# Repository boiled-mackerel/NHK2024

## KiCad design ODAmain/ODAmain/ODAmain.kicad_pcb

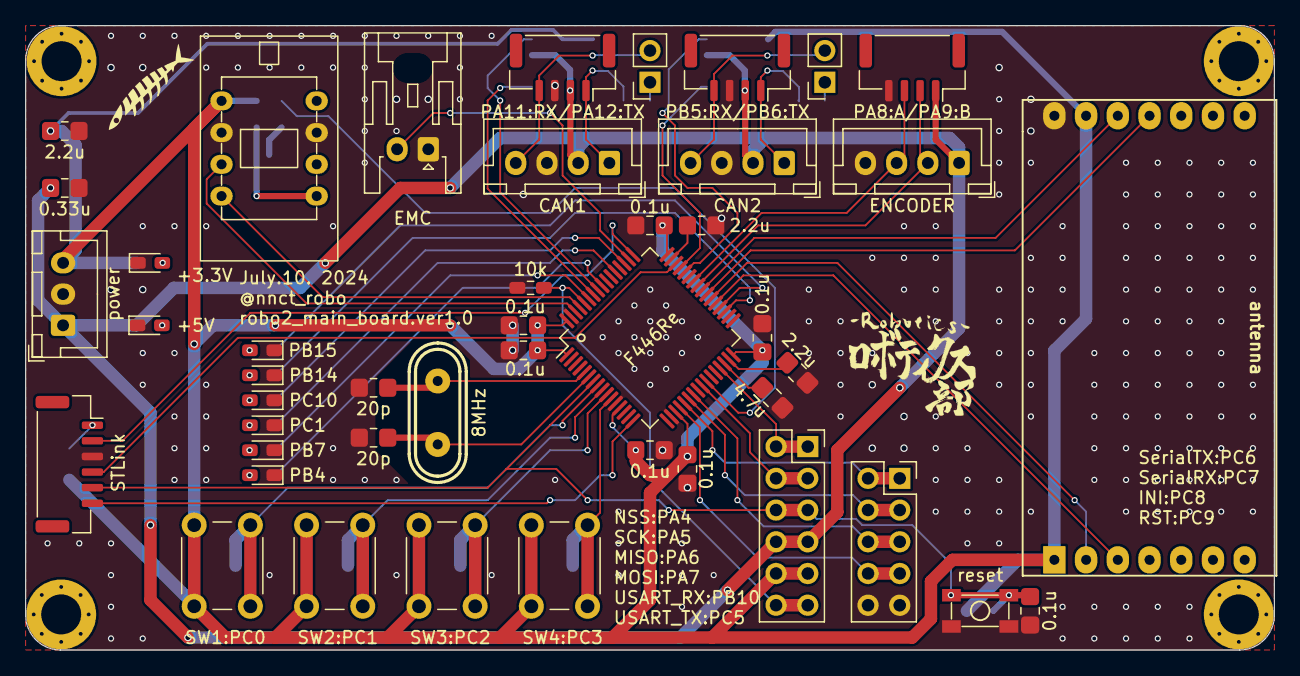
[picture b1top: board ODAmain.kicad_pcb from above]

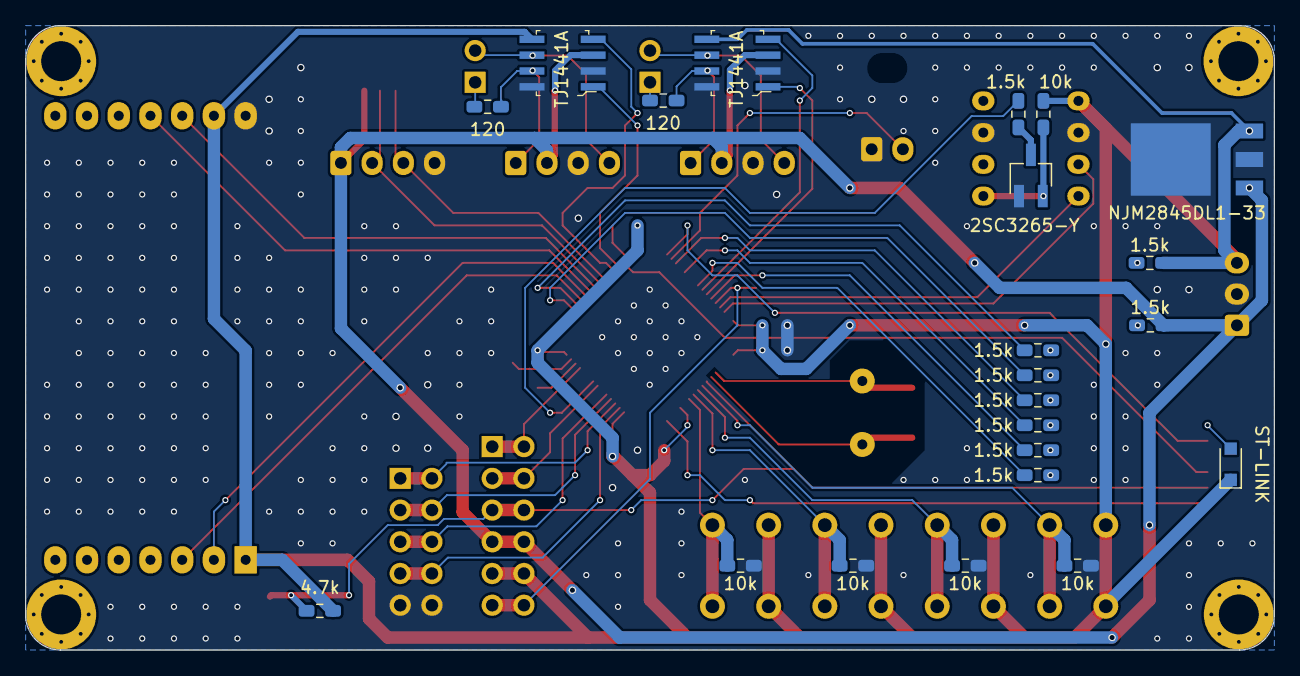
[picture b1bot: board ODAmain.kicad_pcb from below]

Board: 2 copper layers, 100.0 x 50.0 mm, 67 parts (22 on the bottom side), 60 nets.

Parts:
C1: 0.33u; C_0805_2012
C2, C14, C15: 2.2u; C_0805_2012
C3, C6, C8, C9, C10, C11, C12: 0.1u; C_0805_2012
C4, C5: 20p; C_0805_2012
C7: 4.7u; C_0805_2012
D1: PB4; LED_0603_1608
D2: PB7; LED_0603_1608
D3: PC1; LED_0603_1608
D4: PC10; LED_0603_1608
D5: PB14; LED_0603_1608
D6: PB15; LED_0603_1608
D7: +5V; LED_0603_1608
D8: +3.3V; LED_0603_1608
J1: Conn_02x06_Counter_Clockwise; PinSocket_2x06_P2.54mm_Vertical
J2: Conn_02x05_Counter_Clockwise; PinSocket_2x05_P2.54mm_Vertical
J3: Terminate_CAN1; PinSocket_1x02_P2.54mm_Vertical
J4: Terminate_CAN2; PinSocket_1x02_P2.54mm_Vertical
J5: EMC; JST_XA_S02B-XASK-1_1x02_P2.50mm_Horizontal
J6: CAN_1; JST_XH_B4B-XH-A_1x04_P2.50mm_Vertical
J7: CAN_2; JST_XH_B4B-XH-A_1x04_P2.50mm_Vertical
J8: ENCODER1; JST_XH_B4B-XH-A_1x04_P2.50mm_Vertical
J9: gh:CAN_1; JST_GH_SM04B-GHS-TB_1x04-1MP_P1.25mm_Horizontal
J10: gh:CAN_2; JST_GH_SM04B-GHS-TB_1x04-1MP_P1.25mm_Horizontal
J11: gh:ENCODER1; JST_GH_SM04B-GHS-TB_1x04-1MP_P1.25mm_Horizontal
Q1: 2SC3265-Y; 2sc3265_SC-59_Handsoldering
R1, R2: 120; R_0603_1608
R3, R4, R5, R6, R7, R8, R9, R10, R11: 1.5k; R_0603_1608
R12: 4.7k; R_0603_1608
R13, R14, R15, R16, R17, R18: 10k; R_0603_1608
SW1:PC0, SW2:PC1, SW3:PC2, SW4:PC3: SW_Push; SW_PUSH_6mm
U1, U2: TJA1441AT; SOIC-8_IR2302_TJA1441AT
U3: D_Schottky; smd_diode_SOD-323_HandSoldering_cus10f30
U4: power; JST_XH_B3B-XH-A_1x03_P2.50mm_Vertical
U5: ST-LINK; JST_GH_SM06B-GHS-TB_1x06-1MP_P1.25mm_Horizontal
U6: NJM2845DL1-33
U7: BNO055
U8: reset; tact_sw_smd_skrpabe10
U9: FEP-02; FEP-02_PIN_SOCKET
U11: STM32F446RETx-stm32; LQFP-64_10x10mm_P0.5mm
Y1: 8MHz; crystal_hc-49u

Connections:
+3.3V: C2.1, C6.1, C8.1, C9.1, C10.1, C11.1, C12.1, J1.9, J1.10, R10.1, R12.1, R13.2, SW1:PC0.1, SW2:PC1.1, SW3:PC2.1, SW4:PC3.1, U1.5 (VIO), U2.5 (VIO), U3.1 (K), U4.3, U6.3 (Vout), U7.1 (VIN), U9.1 (VCC(2.5v-5.5v)), U9.13 (PowerOn), U11.1 (VBAT), U11.13 (VDDA), U11.19 (VDD), U11.32 (VDD), U11.48 (VDD), U11.64 (VDD)
+5V: C1.1, J1.7, J1.8, J6.2, J7.2, J8.1, J9.2, J10.2, J11.1, R9.1, U1.3 (VDD), U2.3 (VDD), U4.1, U6.1 (Vin)
BNO_RESET: R11.1, U11.26 (ADC1_IN8/ADC2_IN8/I2S3_SD/SDIO_D1/SPI3_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)
BNO_SCL: U7.4 (SCL), U11.61 (CAN1_RX/DCMI_D6/I2C1_SCL/SDIO_D4/TIM10_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)
BNO_SDA: U7.3 (SDA), U11.62 (CAN1_TX/DAC_EXTI9/DCMI_D7/I2C1_SDA/I2S2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)
BOOT0: J1.11, J1.12, R18.2, U11.60 (BOOT0)
CAN1H: J6.1, J9.1, R1.1, U1.7 (CANH)
CAN1L: J3.2, J6.4, J9.4, U1.6 (CANL)
CAN2H: J7.1, J10.1, R2.1, U2.7 (CANH)
CAN2L: J4.2, J7.4, J10.4, U2.6 (CANL)
D4_CAN2RX: U2.4 (RXD), U11.57 (CAN2_RX/DCMI_D10/I2C1_SMBA/I2S1_SD/I2S3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)
D10_CAN2TX: U2.1 (TXD), U11.58 (CAN2_TX/CEC/DCMI_D5/I2C1_SCL/QUADSPI_BK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)
D14_CAN1TX: U1.1 (TXD), U11.45 (CAN1_TX/TIM1_ETR/USART1_RTS/USB_OTG_FS_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)
D15_CAN1RX: U1.4 (RXD), U11.44 (ADC1_EXTI11/ADC2_EXTI11/ADC3_EXTI11/CAN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)
EMC: J5.2, U11.50 (ADC1_EXTI15/ADC2_EXTI15/ADC3_EXTI15/CEC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)
FEP_INI: U9.11 (/INI), U11.39 (PC8/DCMI_D2/SDIO_D0/SYS_TRACED0/TIM3_CH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)
FEP_RST: U9.12 (/RST), U11.40 (PC9/DAC_EXTI9/DCMI_D3/I2C3_SDA/I2S_CKIN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)
GND: C1.2, C2.2, C3.2, C4.1, C5.1, C6.2, C7.2, C8.2, C9.2, C10.2, C11.2, C12.2, C14.2, C15.2, D1.1 (K), D2.1 (K), D3.1 (K), D4.1 (K), D5.1 (K), D6.1 (K), D7.1 (K), D8.1 (K), J2.9, J2.10, J5.1, J6.3, J7.3, J8.4, J9.3, J10.3, J11.4, Q1.1 (E), R14.2, R15.2, R16.2, R17.2, R18.1, U1.2 (GND), U1.8 (S), U2.2 (GND), U2.8 (S), U4.2, U5.3, U6.2 (GND), U7.2 (GND), U7.7 (GND), U8.2, U8.4, U9.14 (GND), U11.12 (VSSA), U11.18 (VSS), U11.63 (VSS)
LED1: R8.1, U11.36 (ADC1_EXTI15/ADC2_EXTI15/ADC3_EXTI15/I2S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)
LED2: R7.1, U11.35 (SPI2_MISO/TIM12_CH1/TIM1_CH2N/TIM8_CH2N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)
LED3: R6.1, U11.51 (PC10/DCMI_D8/I2S3_CK/QUADSPI_BK1_IO1/SD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)
LED4: R5.1, U11.53 (PC12/DCMI_D9/I2C2_SDA/I2S3_SD/SDIO_CK/S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)
LED5: R4.1, U11.59 (DCMI_VSYNC/I2C1_SDA/SPDIFRX_IN0/TIM4_CH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)
LED6: R3.1, U11.56 (I2C3_SDA/I2S2_WS/SPI1_MISO/SPI2_NSS/SPI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)
MISO: J2.3, J2.4, U11.22 (ADC1_IN6/ADC2_IN6/DCMI_PIXCLK/I2S2_MCK/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)
MOSI: J2.5, J2.6, U11.23 (ADC1_IN7/ADC2_IN7/I2S1_SD/SPI1_MOSI/TIM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)
NSS: J2.7, J2.8, U11.20 (ADC1_IN4/ADC2_IN4/DAC_OUT1/DCMI_HSYNC/I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)
unnamed: C14.1, U11.47 (VSS)
unnamed: C15.1, U11.31 (VSS)
unnamed: D1.2 (A), R3.2
unnamed: D2.2 (A), R4.2
unnamed: D3.2 (A), R5.2
unnamed: D4.2 (A), R6.2
unnamed: D5.2 (A), R7.2
unnamed: D6.2 (A), R8.2
unnamed: D7.2 (A), R9.2
unnamed: D8.2 (A), R10.2
unnamed: J3.1, R1.2
unnamed: J4.1, R2.2
unnamed: Q1.3 (B), R11.2
unnamed: Q1.2 (C), R13.1, U7.5 (RESET)
unnamed: U3.2 (A), U5.1
unnamed: C4.2, U11.5 (PH0/RCC_OSC_IN), Y1.2
unnamed: C5.2, U11.6 (PH1/RCC_OSC_OUT), Y1.1
unnamed: C7.1, U11.30 (VCAP_1)
PC_6_Serial6TX: U9.3 (TXD(DataIn)), U11.37 (PC6/DCMI_D0/FMPI2C1_SCL/I2S2_MCK/SDIO_D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)
PC_7_Serial6RX: U9.2 (RXD(DateOut)), U11.38 (PC7/DCMI_D1/FMPI2C1_SDA/I2S2_CK/I2S3_MC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)
RESET: C3.1, J1.5, J1.6, R12.2, U5.5, U8.1, U8.3, U11.7 (NRST)
SCK: J2.1, J2.2, U11.21 (ADC1_IN5/ADC2_IN5/DAC_OUT2/I2S1_CK/SPI1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)
ST-LINK(TX): U5.6, U11.16 (ADC1_IN2/ADC2_IN2/ADC3_IN2/TIM2_CH3/TIM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)
SW1: R14.1, SW1:PC0.2, U11.8 (PC0/ADC1_IN10/ADC2_IN10/ADC3_IN10/SAI1_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)
SW2: R15.1, SW2:PC1.2, U11.9 (PC1/ADC1_IN11/ADC2_IN11/ADC3_IN11/I2S2_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)
SW3: R16.1, SW3:PC2.2, U11.10 (PC2/ADC1_IN12/ADC2_IN12/ADC3_IN12/SPI2_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)
SW4: R17.1, SW4:PC3.2, U11.11 (PC3/ADC1_IN13/ADC2_IN13/ADC3_IN13/I2S2_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)
SWCLK: U5.2, U11.49 (SYS_JTCK-SWCLK/PA14)
SWDIO: U5.4, U11.46 (SYS_JTMS-SWDIO/PA13)
TIM1_1: J8.2, J11.2, U11.41 (I2C3_SCL/RCC_MCO_1/TIM1_CH1/USART1_CK/U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)
TIM1_2: J8.3, J11.3, U11.42 (DAC_EXTI9/DCMI_D0/I2C3_SMBA/I2S2_CK/SAI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)
U0RXD: J1.1, J1.2, U11.29 (I2C2_SCL/I2S2_CK/SAI1_SCK_A/SPI2_SCK/TI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)
U0TXD: J1.3, J1.4, U11.25 (PC5/ADC1_IN15/ADC2_IN15/SPDIFRX_IN3/USA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)

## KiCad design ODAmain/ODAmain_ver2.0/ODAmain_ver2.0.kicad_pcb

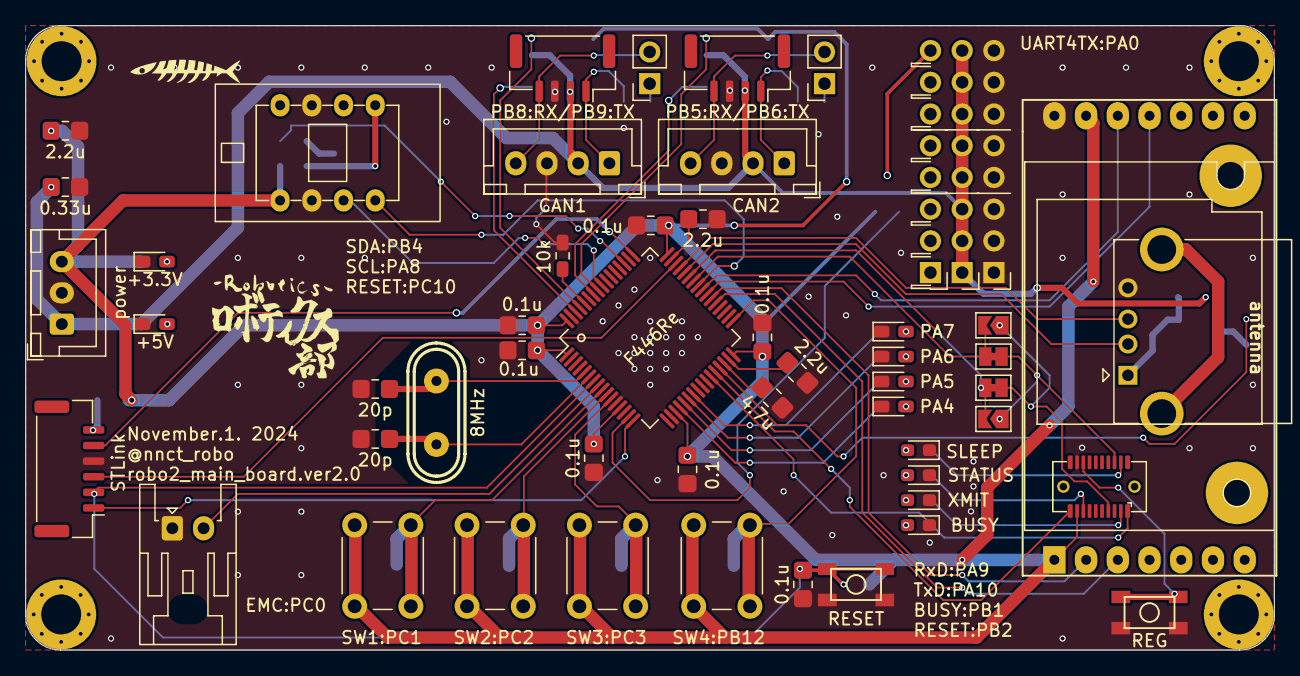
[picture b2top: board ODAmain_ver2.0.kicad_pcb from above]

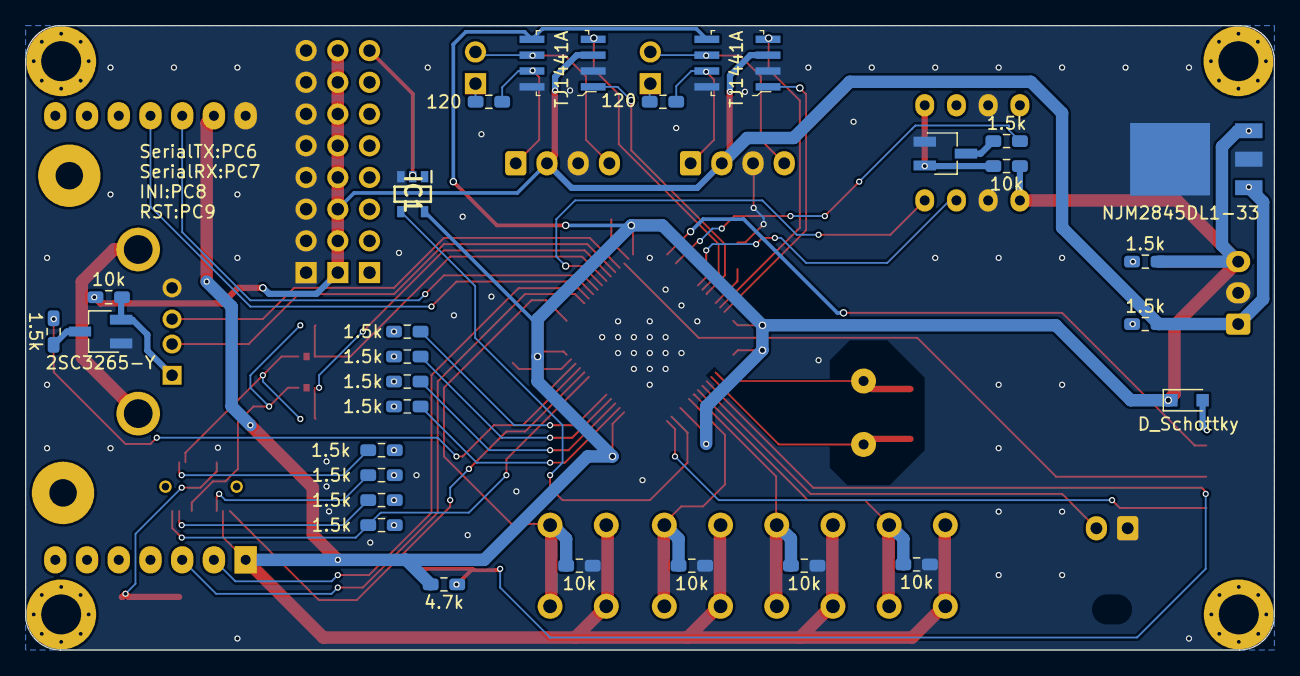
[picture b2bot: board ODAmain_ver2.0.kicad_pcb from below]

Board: 2 copper layers, 100.0 x 50.0 mm, 79 parts (28 on the bottom side), 69 nets.

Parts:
C1: 0.33u; C_0805_2012
C2, C8, C9: 2.2u; C_0805_2012
C3, C6, C10, C11, C12, C13, C14: 0.1u; C_0805_2012
C4, C5: 20p; C_0805_2012
C7: 4.7u; C_0805_2012
D3: PA7; LED_0603_1608
D4: PA6; LED_0603_1608
D5: PA5; LED_0603_1608
D6: PA4; LED_0603_1608
D7: +5V; LED_0603_1608
D8: +3.3V; LED_0603_1608
D9: BUSY; LED_0603_1608Metric_Pad1.05x0.95mm_HandSolder
D10: XMIT; LED_0603_1608Metric_Pad1.05x0.95mm_HandSolder
D11: SLEEP; LED_0603_1608Metric_Pad1.05x0.95mm_HandSolder
D12: STATUS; LED_0603_1608Metric_Pad1.05x0.95mm_HandSolder
IC1: BD7LS04G-CTL; SOT95P280X125-5N
J1: EMC; JST_XA_S02B-XASK-1_1x02_P2.50mm_Horizontal
J2: Terminate_CAN1; PinSocket_1x02_P2.54mm_Vertical
J3: Terminate_CAN2; PinSocket_1x02_P2.54mm_Vertical
J4: CAN_1; JST_XH_B4B-XH-A_1x04_P2.50mm_Vertical
J5: CAN_2; JST_XH_B4B-XH-A_1x04_P2.50mm_Vertical
J6: gh:CAN_1; JST_GH_SM04B-GHS-TB_1x04-1MP_P1.25mm_Horizontal
J7: gh:CAN_2; JST_GH_SM04B-GHS-TB_1x04-1MP_P1.25mm_Horizontal
J8: im920sl_USB; USB_A_CONNFLY_DS1095-WNR0
J9: RX==TX; SolderJumper-2_P1.3mm_Bridged_Pad1.0x1.5mm
J10: TX==RX; SolderJumper-2_P1.3mm_Bridged_Pad1.0x1.5mm
J11: RX==RX; SolderJumper-2_P1.3mm_Open_TrianglePad1.0x1.5mm
J12: TX==TX; SolderJumper-2_P1.3mm_Open_TrianglePad1.0x1.5mm
Q1, Q2: 2SC3265-Y; 2sc3265_SC-59_Handsoldering
R2, R3: 120; R_0603_1608
R5, R6, R7, R8, R9, R10, R11, R13, R16, R17, R18, R19: 1.5k; R_0603_1608
R12, R14, R20, R21, R22, R23, R24: 10k; R_0603_1608
R15: 4.7k; R_0603_1608
SW1: SW1:PC1; SW_PUSH_6mm
SW2: SW2:PC2; SW_PUSH_6mm
SW3: SW3:PC3; SW_PUSH_6mm
SW4: SW4:PB12; SW_PUSH_6mm
U1: D_Schottky; smd_diode_SOD-323_HandSoldering_cus10f30
U2, U3: TJA1441AT; SOIC-8_IR2302_TJA1441AT
U4: power; JST_XH_B3B-XH-A_1x03_P2.50mm_Vertical
U5: ST-LINK; JST_GH_BM06B-GHS-TBT_1x06-1MP_P1.25mm_Vertical
U6: NJM2845DL1-33
U7: BNO055
U8: FEP-02; FEP-02_PIN_SOCKET
U9: IM920sL
U10: RESET; tact_sw_smd_skrpabe10
U11: REG; tact_sw_smd_skrpabe10
U12: R3006SB
U13: stm32_f446re; LQFP-64_10x10mm_P0.5mm
Y1: 8MHz; crystal_hc-49u

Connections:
+3.3V: C2.1, C6.1, C10.1, C11.1, C12.1, C13.1, C14.1, IC1.5 (VCC), R13.1, R14.2, R15.1, SW1.1, SW2.1, SW3.1, SW4.1, U1.1 (K), U2.5 (VIO), U3.5 (VIO), U4.3, U6.3 (Vout), U7.1 (VIN), U8.1 (VCC(2.5v-5.5v)), U8.13 (PowerOn), U9.17 (VCC), U13.1 (VBAT), U13.13 (VDDA), U13.19 (VDD), U13.32 (VDD), U13.48 (VDD), U13.64 (VDD)
+5V: C1.1, J4.2, J5.2, J6.2, J7.2, R10.1, R12.2, U2.3 (VDD), U3.3 (VDD), U4.1, U6.1 (Vin), U12.2 (5V)
BNO_RESET: R11.1, U13.51 (PC10)
BNO_SCL: U7.4 (SCL), U13.41 (PA8)
BNO_SDA: U7.3 (SDA), U13.56 (PB4)
BOOT0: R24.2, U13.60 (BOOT0)
CAN1H: J4.1, J6.1, R2.1, U2.7 (CANH)
CAN1L: J2.2, J4.4, J6.4, U2.6 (CANL)
CAN1_RX: U2.4 (RXD), U13.61 (PB8)
CAN1_TX: U2.1 (TXD), U13.62 (PB9)
CAN2H: J5.1, J7.1, R3.1, U3.7 (CANH)
CAN2L: J3.2, J5.4, J7.4, U3.6 (CANL)
CAN2_RX: U3.4 (RXD), U13.57 (PB5)
CAN2_TX: U3.1 (TXD), U13.58 (PB6)
EMC: J1.2, U13.8 (PC0)
FEP_INI: U8.11 (/INI), U13.39 (PC8)
FEP_RST: U8.12 (/RST), U13.40 (PC9)
GND: C1.2, C2.2, C3.2, C4.1, C5.1, C6.2, C7.2, C8.2, C9.2, C10.2, C11.2, C12.2, C13.2, C14.2, D3.1 (K), D4.1 (K), D5.1 (K), D6.1 (K), D7.1 (K), D8.1 (K), D9.1 (K), D10.1 (K), D11.1 (K), D12.1 (K), IC1.3 (GND), J1.1, J4.3, J5.3, J6.3, J7.3, J8.4 (GND), Q1.1 (E), Q2.1 (E), R20.2, R21.2, R22.2, R23.2, R24.1, U2.2 (GND), U2.8 (S), U3.2 (GND), U3.8 (S), U4.2, U5.4, U6.2 (GND), U7.2 (GND), U7.7 (GND), U8.14 (GND), U9.18 (GND), U10.2, U10.4, U11.2, U11.4, U12.1 (GND), U13.12 (VSSA), U13.18 (VSS), U13.63 (VSS)
LED1: R8.1, U13.20 (PA4)
LED2: R7.1, U13.21 (PA5)
LED3: R6.1, U13.22 (PA6)
LED4: R5.1, U13.23 (PA7)
unnamed: C8.1, U13.31 (VSS)
unnamed: C9.1, U13.47 (VSS)
unnamed: D3.2 (A), R5.2
unnamed: D4.2 (A), R6.2
unnamed: D5.2 (A), R7.2
unnamed: D6.2 (A), R8.2
unnamed: D7.2 (A), R10.2
unnamed: D8.2 (A), R13.2
unnamed: D9.2 (A), R16.2
unnamed: D10.2 (A), R17.2
unnamed: D11.2 (A), R18.2
unnamed: D12.2 (A), R19.2
unnamed: J2.1, R2.2
unnamed: J3.1, R3.2
unnamed: J8.1 (VBUS), Q1.2 (C), R12.1
unnamed: J10.2, J11.2, U13.43 (PA10)
unnamed: J9.2, J12.2, U13.42 (PA9)
unnamed: Q1.3 (B), R9.2
unnamed: Q2.3 (B), R11.2
unnamed: Q2.2 (C), R14.1, U7.5 (RESET)
unnamed: U1.2 (A), U5.6
unnamed: R17.1, U9.3 (IO3/XMIT)
unnamed: R18.1, U9.4 (IO4/SLEEP)
unnamed: U9.16 (REG), U11.1, U11.3
unnamed: R19.1, U9.15 (SATUS)
unnamed: C4.2, U13.5 (PH0), Y1.2
unnamed: C5.2, U13.6 (PH1), Y1.1
unnamed: C7.1, U13.30 (VCAP_1)
PC_6_Serial6TX: U8.3 (TXD(DataIn)), U13.37 (PC6)
PC_7_Serial6RX: U8.2 (RXD(DateOut)), U13.38 (PC7)
RST: C3.1, R15.2, U5.2, U10.1, U10.3, U13.7 (NRST)
SBUS: IC1.2 (A), U12.10 (S.BUS)
SW1: R20.1, SW1.2, U13.9 (PC1)
SW2: R21.1, SW2.2, U13.10 (PC2)
SW3: R22.1, SW3.2, U13.11 (PC3)
SW4: R23.1, SW4.2, U13.33 (PB12)
SWCLK: U5.5, U13.49 (PA14)
SWDIO: U5.3, U13.46 (PA13)
UART2_TX(STLINK): U5.1, U13.16 (PA2)
UART4_RX: IC1.4 (Y), U13.15 (PA1)
im920sl_BUSY: R16.1, U9.1 (BUSY), U13.27 (PB1)
im920sl_D+: J8.3 (D+), U13.45 (PA12)
im920sl_D-: J8.2 (D-), U13.44 (PA11)
im920sl_RESET: U9.19 (RESET), U13.28 (PB2)
im920sl_RxD: J9.1, J11.1, U9.6 (RxD)
im920sl_TxD: J10.1, J12.1, U9.7 (TxD)
im920sl_zettairesetsaseruMAN: R9.1, U13.29 (PB10)

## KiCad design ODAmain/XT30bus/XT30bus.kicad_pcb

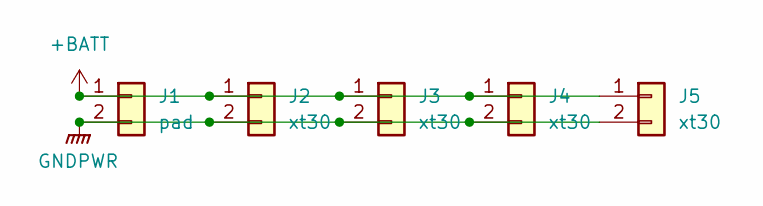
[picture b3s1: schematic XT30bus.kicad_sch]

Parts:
J1: pad; POWER_PAD_normal
J2, J3, J4, J5: xt30; AMASS_XT30U-F_1x02_P5.0mm_Vertical

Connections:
+BATT: J1.1, J2.1, J3.1, J4.1, J5.1
GNDPWR: J1.2, J2.2, J3.2, J4.2, J5.2

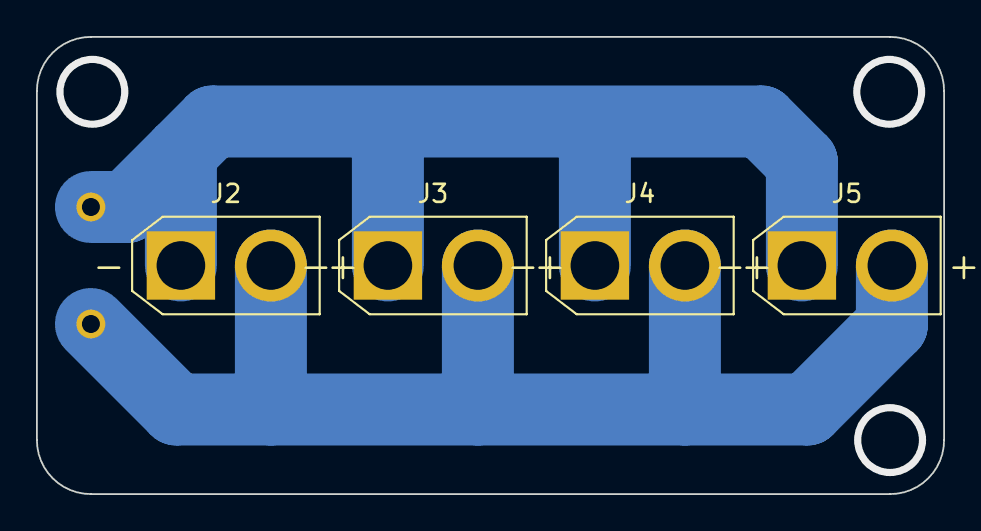
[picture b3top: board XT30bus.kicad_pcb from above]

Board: 2 copper layers, 50.4 x 25.4 mm, 5 parts (1 on the bottom side), 2 nets.

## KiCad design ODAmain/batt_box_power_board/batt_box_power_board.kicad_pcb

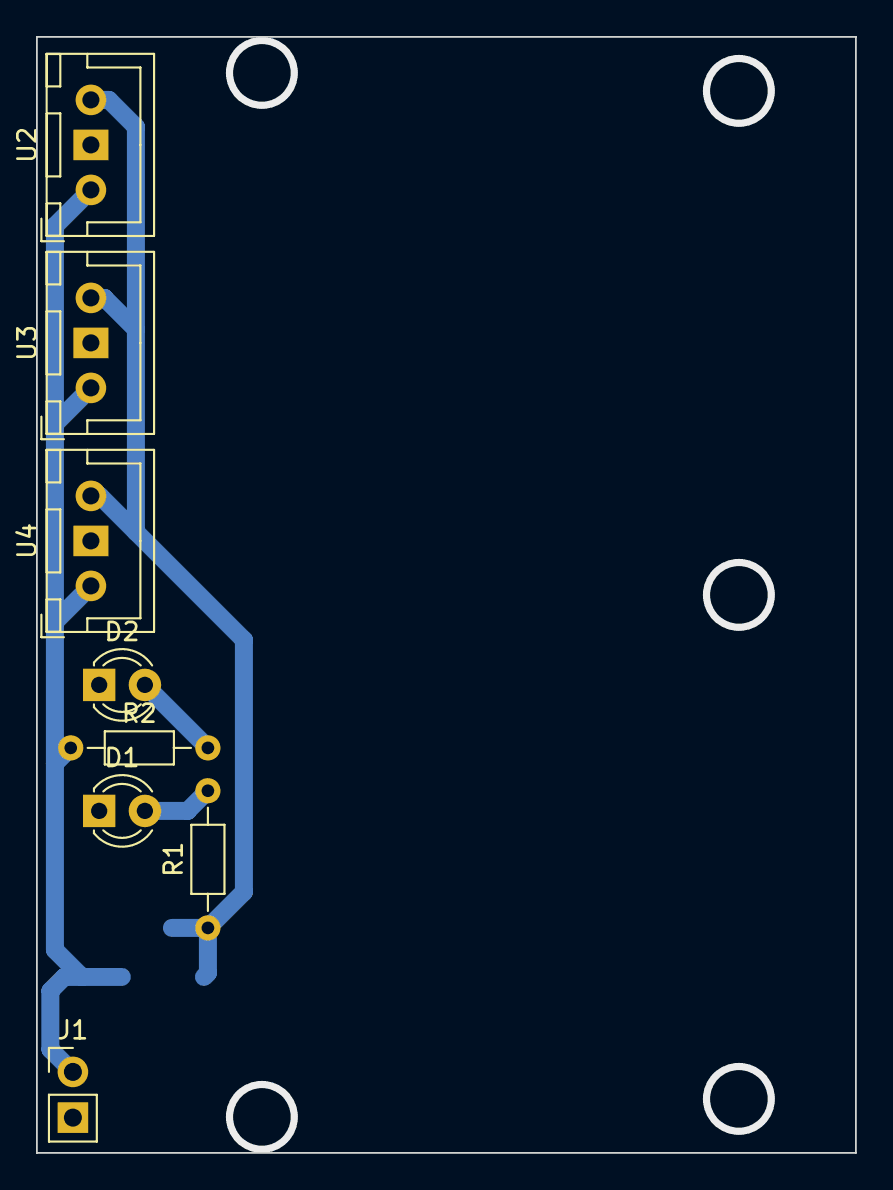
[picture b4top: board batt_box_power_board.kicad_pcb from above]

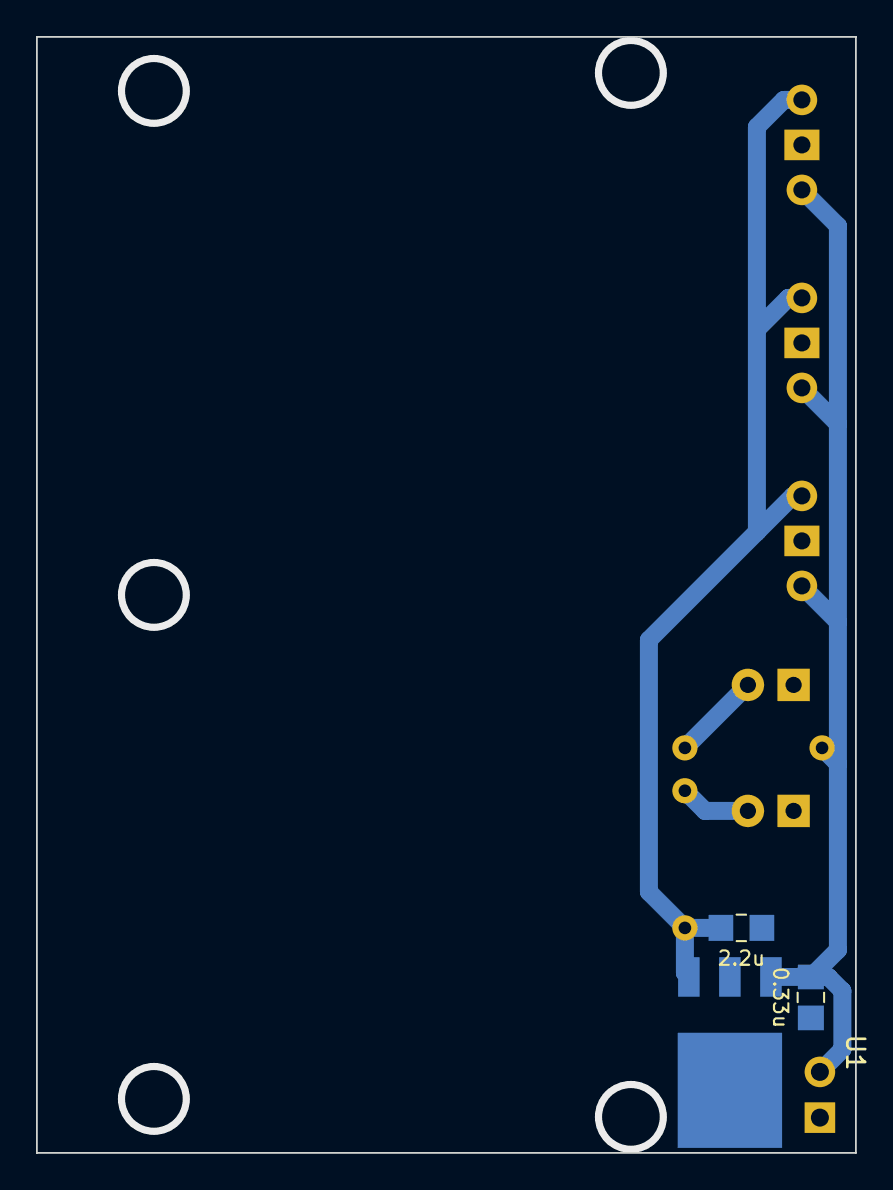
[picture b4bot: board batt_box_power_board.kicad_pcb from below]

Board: 2 copper layers, 45.5 x 62.0 mm, 11 parts (3 on the bottom side), 5 nets.

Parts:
C1: 0.33u; C_0805_2012
C2: 2.2u; C_0805_2012
D1: +3.3V; LED_D3.0mm
D2: +5V; LED_D3.0mm
J1: IN; PinHeader_1x02_P2.54mm_Vertical
R1, R2: 1.5k; R_Axial_DIN0204_L3.6mm_D1.6mm_P7.62mm_Horizontal
U1: NJM2845DL1-33
U2, U3, U4: power; JST_XH_B3B-XH-A_1x03_P2.50mm_Vertical

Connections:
+3.3V: C2.1, R1.1, U1.3 (Vout), U2.3, U3.3, U4.3
BAT: C1.1, J1.1, R2.1, U1.1 (Vin), U2.1, U3.1, U4.1
GND: C1.2, C2.2, D1.1 (K), D2.1 (K), J1.2, U1.2 (GND), U2.2, U3.2, U4.2
unnamed: D1.2 (A), R1.2
unnamed: D2.2 (A), R2.2

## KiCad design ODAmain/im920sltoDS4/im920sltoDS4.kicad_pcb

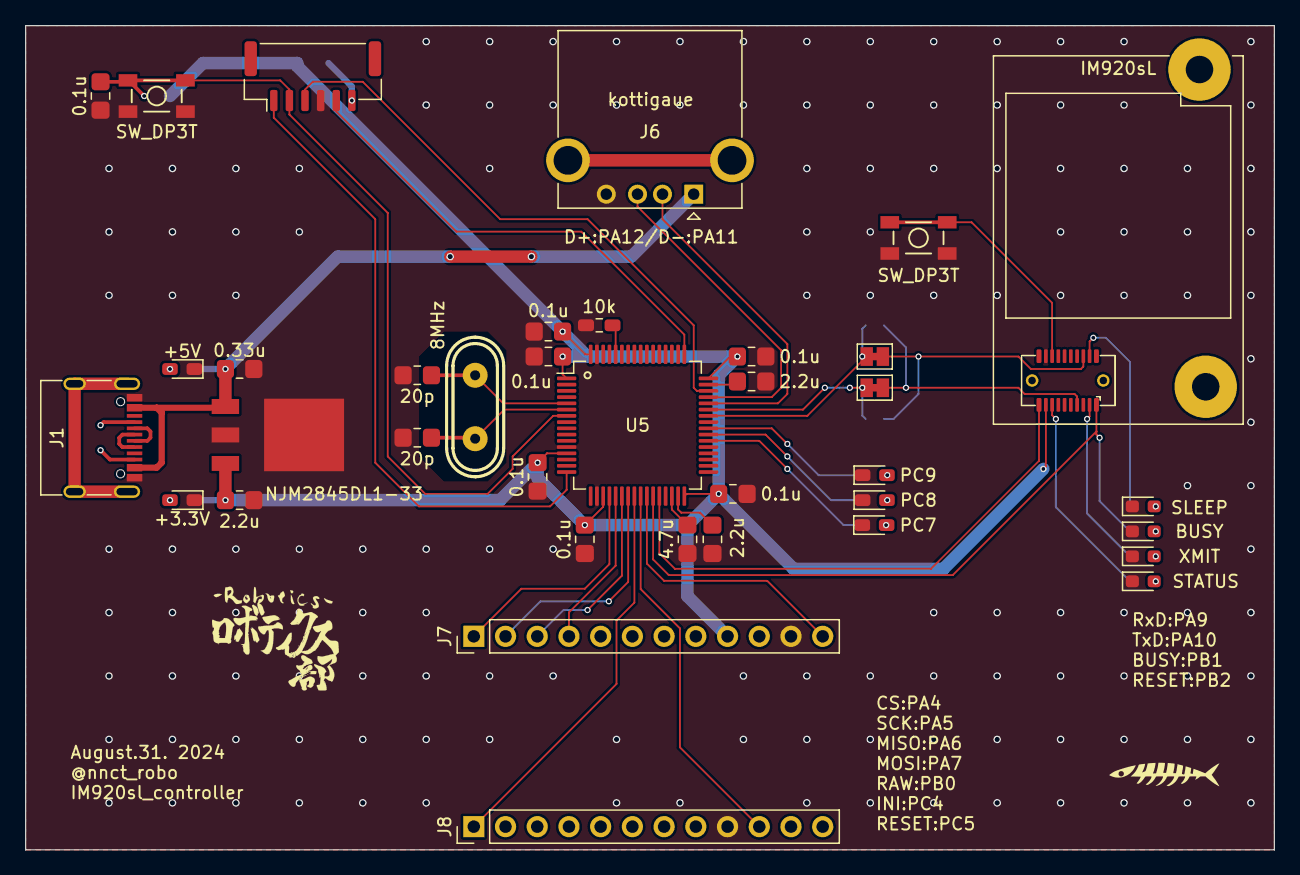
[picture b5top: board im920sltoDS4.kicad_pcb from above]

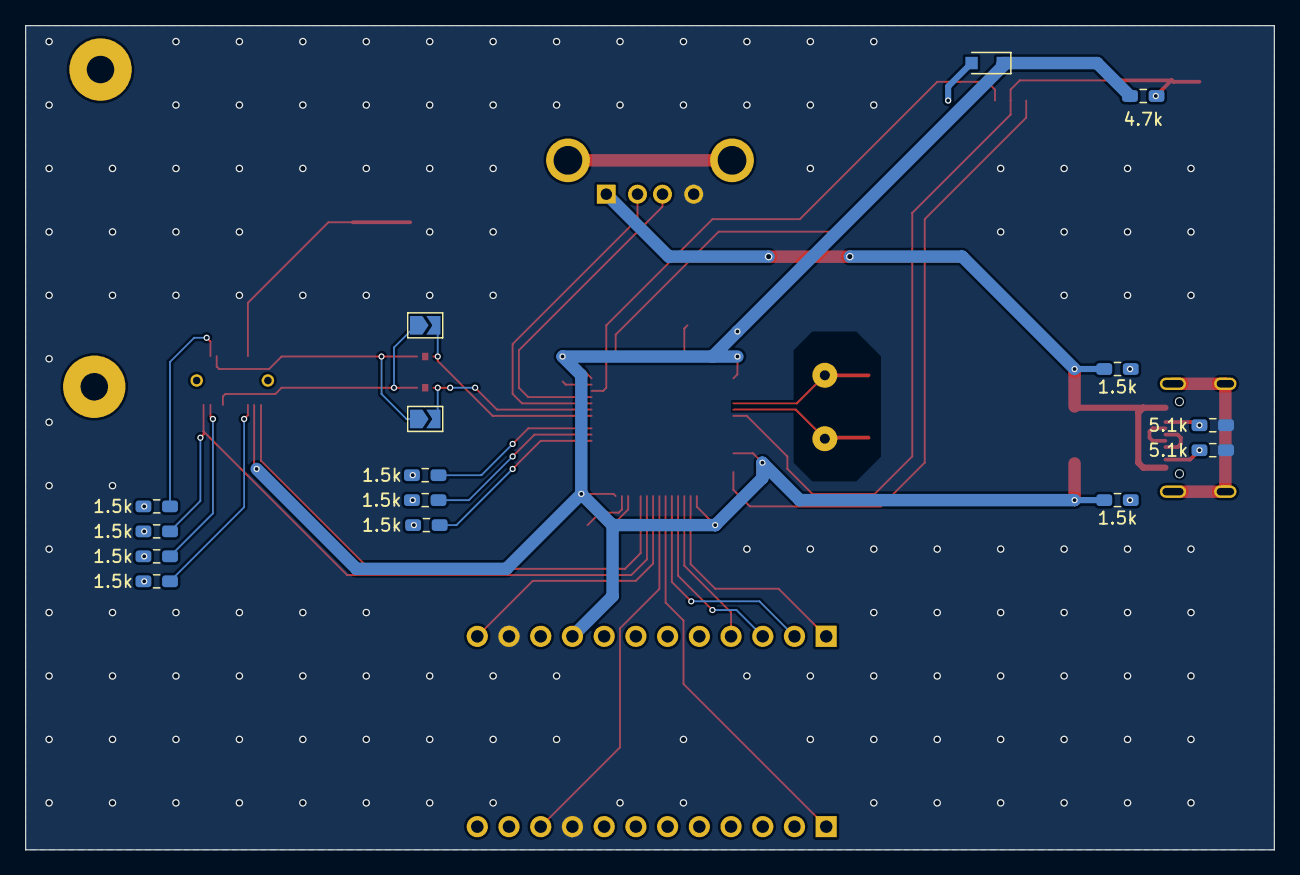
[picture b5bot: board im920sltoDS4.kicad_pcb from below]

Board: 2 copper layers, 100.0 x 66.0 mm, 52 parts (15 on the bottom side), 49 nets.

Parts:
C1: 0.33u; C_0805_2012
C2, C8, C9: 2.2u; C_0805_2012
C3, C4: 20p; C_0805_2012
C5, C6, C10, C11, C12, C13, C14: 0.1u; C_0805_2012
C7: 4.7u; C_0805_2012
D1: +5V; LED_0603_1608
D2: +3.3V; LED_0603_1608
D3: BUSY; LED_0603_1608Metric_Pad1.05x0.95mm_HandSolder
D4: XMIT; LED_0603_1608Metric_Pad1.05x0.95mm_HandSolder
D5: SLEEP; LED_0603_1608Metric_Pad1.05x0.95mm_HandSolder
D6: STATUS; LED_0603_1608Metric_Pad1.05x0.95mm_HandSolder
D10: PC7; LED_0603_1608
D11: PC8; LED_0603_1608
D12: PC9; LED_0603_1608
J1: USB_C_Receptacle_USB2.0; USB_C_Receptacle_G-Switch_GT-USB-7010ASV
J2: RX==TX; SolderJumper-2_P1.3mm_Bridged_Pad1.0x1.5mm
J3: TX==RX; SolderJumper-2_P1.3mm_Bridged_Pad1.0x1.5mm
J4: RX==RX; SolderJumper-2_P1.3mm_Open_TrianglePad1.0x1.5mm
J5: TX==TX; SolderJumper-2_P1.3mm_Open_TrianglePad1.0x1.5mm
J6: DS4_USB; USB_A_CONNFLY_DS1095-WNR0
J7: usb_host_spi_1; PinHeader_1x12_P2.54mm_Vertical
J8: usb_host_spi_2; PinHeader_1x12_P2.54mm_Vertical
R1, R2: 5.1k; R_0603_1608
R3, R4, R7, R8, R9, R10, R14, R15, R16: 1.5k; R_0603_1608
R5: 4.7k; R_0603_1608
R6: 10k; R_0603_1608
U1: NJM2845DL1-33
U2: D_Schottky; smd_diode_SOD-323_HandSoldering_cus10f30
U3: ST-LINK; JST_GH_BM06B-GHS-TBT_1x06-1MP_P1.25mm_Vertical
U4, U7: SW_DP3T; tact_sw_smd_skrpabe10
U5: stm32_f446re; LQFP-64_10x10mm_P0.5mm
U6: IM920sL
Y1: 8MHz; crystal_hc-49u

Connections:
+3.3V: C2.1, C6.1, C10.1, C11.1, C12.1, C13.1, C14.1, J7.9, R4.1, R5.1, U1.3 (Vout), U2.1 (K), U5.1 (VBAT), U5.13 (VDDA), U5.19 (VDD), U5.32 (VDD), U5.48 (VDD), U5.64 (VDD), U6.17 (VCC)
+5V: C1.1, J1.A4 (VBUS), J1.A9 (VBUS), J1.B4 (VBUS), J1.B9 (VBUS), J6.1 (VBUS), R3.1, U1.1 (Vin)
CS: J7.1, U5.20 (PA4)
DS4_D+: J6.3 (D+), U5.45 (PA12)
DS4_D-: J6.2 (D-), U5.44 (PA11)
GND: C1.2, C2.2, C3.1, C4.1, C5.2, C6.2, C7.2, C8.2, C9.2, C10.2, C11.2, C12.2, C13.2, C14.2, D1.1 (K), D2.1 (K), D3.1 (K), D4.1 (K), D5.1 (K), D6.1 (K), D10.1 (K), D11.1 (K), D12.1 (K), J1.A1 (GND), J1.A12 (GND), J1.B1 (GND), J1.B12 (GND), J6.4 (GND), J7.11, J8.9, R1.2, R2.2, R6.1, U1.2 (GND), U3.4, U4.2, U4.4, U5.12 (VSSA), U5.18 (VSS), U5.63 (VSS), U6.18 (GND), U7.2, U7.4
INI: J8.1, U5.24 (PC4)
LED1: R16.1, U5.40 (PC9)
LED2: R15.1, U5.39 (PC8)
LED3: R14.1, U5.38 (PC7)
MISO: J7.3, U5.22 (PA6)
MOSI: J7.2, U5.23 (PA7)
unnamed: C8.1, U5.31 (VSS)
unnamed: C9.1, U5.47 (VSS)
unnamed: D1.2 (A), R3.2
unnamed: D2.2 (A), R4.2
unnamed: D3.2 (A), R7.2
unnamed: D4.2 (A), R8.2
unnamed: D5.2 (A), R9.2
unnamed: D6.2 (A), R10.2
unnamed: D10.2 (A), R14.2
unnamed: D11.2 (A), R15.2
unnamed: D12.2 (A), R16.2
unnamed: J1.A5 (CC1), R1.1
unnamed: J1.B5 (CC2), R2.1
unnamed: J1.A6 (D+), J1.B6 (D+)
unnamed: J1.A7 (D-), J1.B7 (D-)
unnamed: J2.2, J5.2, U5.42 (PA9)
unnamed: J3.2, J4.2, U5.43 (PA10)
unnamed: U2.2 (A), U3.6
unnamed: R6.2, U5.60 (BOOT0)
unnamed: C3.2, U5.5 (PH0), Y1.2
unnamed: C4.2, U5.6 (PH1), Y1.1
unnamed: C7.1, U5.30 (VCAP_1)
unnamed: R8.1, U6.3 (IO3/XMIT)
unnamed: R9.1, U6.4 (IO4/SLEEP)
unnamed: U6.16 (REG), U7.1, U7.3
unnamed: R10.1, U6.15 (SATUS)
RAW: J7.12, U5.26 (PB0)
RESET: J8.10, U5.25 (PC5)
RST: C5.1, R5.2, U3.2, U4.1, U4.3, U5.7 (NRST)
SCK: J7.4, U5.21 (PA5)
SWCLK: U3.5, U5.49 (PA14)
SWDIO: U3.3, U5.46 (PA13)
URTA2_TX(STLINK): U3.1, U5.16 (PA2)
im920sl_BUSY: R7.1, U5.27 (PB1), U6.1 (BUSY)
im920sl_RESET: U5.28 (PB2), U6.19 (RESET)
im920sl_RxD: J2.1, J4.1, U6.6 (RxD)
im920sl_TxD: J3.1, J5.1, U6.7 (TxD)

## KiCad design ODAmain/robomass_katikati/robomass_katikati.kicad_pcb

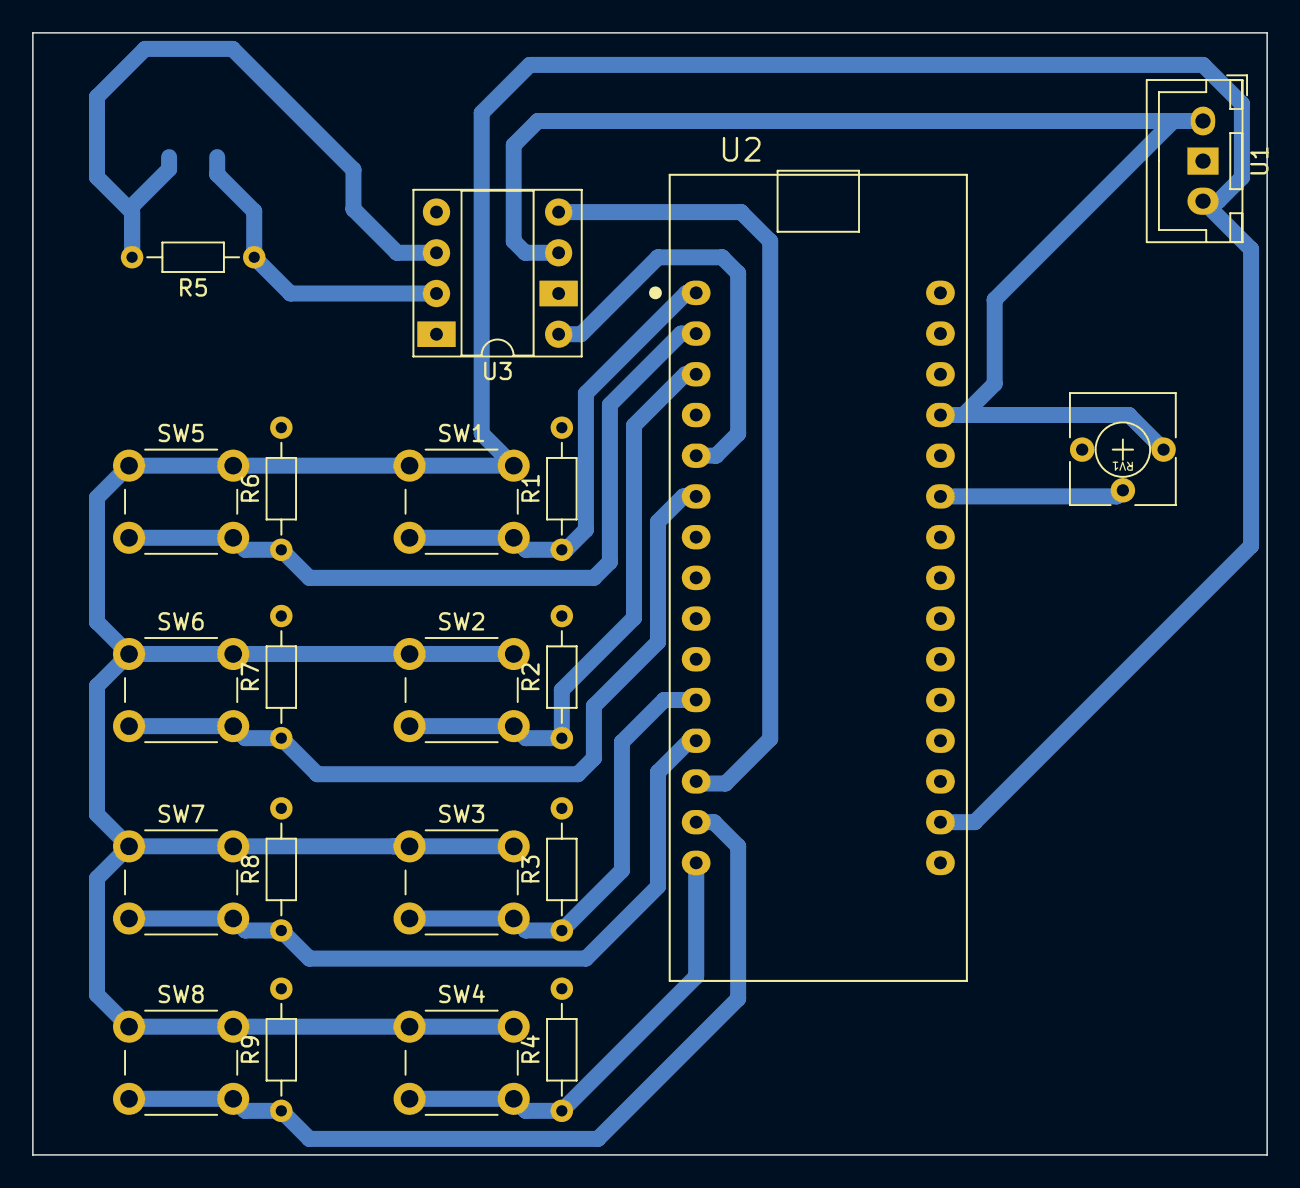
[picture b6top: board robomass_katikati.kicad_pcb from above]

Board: 2 copper layers, 77.0 x 70.0 mm, 22 parts (1 on the bottom side), 16 nets.

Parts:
J1: robomass_gh; JST_GH_BM02B-GHS-TBT_1x02-1MP_P1.25mm_Vertical
R1, R2, R3, R4, R6, R7, R8, R9: 10k; R_Axial_DIN0204_L3.6mm_D1.6mm_P7.62mm_Horizontal
R5: 120; R_Axial_DIN0204_L3.6mm_D1.6mm_P7.62mm_Horizontal
RV1: R_Potentiometer; Potentiometer_3362p
SW1, SW2, SW3, SW4, SW5, SW6, SW7, SW8: SW_Push; SW_PUSH_6mm
U1: power; JST_XH_B3B-XH-A_1x03_P2.50mm_Vertical
U2: NucleoF303K8; MODULE_NUCLEO-F303K8
U3: MCP2561-E-P; DIP-8_W7.62mm_Socket_LongPads

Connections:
+3.3V: SW1.1, SW2.1, SW3.1, SW4.1, SW5.1, SW6.1, SW7.1, SW8.1, U1.3, U2.17 (3V3)
+5V: RV1.1, U1.1, U2.27 (5V), U3.3 (VDD)
CAN1_RX: U2.13 (D10/PA_11/CAN1_RD), U3.4 (RXD)
CAN1_TX: U2.5 (D2/PA_12/CAN1_TD), U3.1 (TXD)
GND: R1.2, R2.2, R3.2, R4.2, R6.2, R7.2, R8.2, R9.2, RV1.3, U1.2, U2.4 (GND), U2.29 (GND), U3.2 (VSS), U3.8 (STBY)
unnamed: J1.1, R5.1, U3.7 (CANH)
unnamed: J1.2, R5.2, U3.6 (CANL)
unnamed: RV1.2, U2.25 (ADC2_4/PA_7/A6)
SW1: R1.1, SW1.2, U2.1 (D1/PA_9/UART_TX)
SW2: R2.1, SW2.2, U2.3 (NRST)
SW3: R3.1, SW3.2, U2.11 (D8/PA_8)
SW4: R4.1, SW4.2, U2.15 (D12/PB_4/UART2_RX)
SW5: R6.1, SW5.2, U2.2 (D0/PA_10/UART_RX)
SW6: R7.1, SW6.2, U2.6 (D3/PB_0/ADC1_11)
SW7: R8.1, SW7.2, U2.12 (D9/PA_8)
SW8: R9.1, SW8.2, U2.14 (D11/PB_5)
